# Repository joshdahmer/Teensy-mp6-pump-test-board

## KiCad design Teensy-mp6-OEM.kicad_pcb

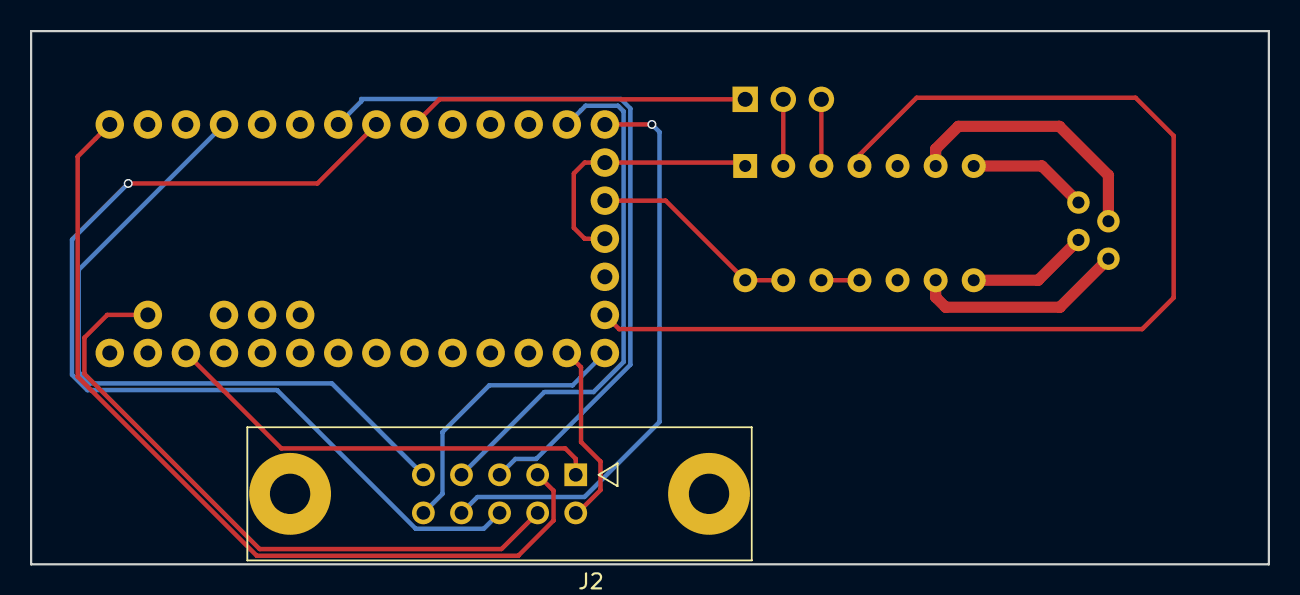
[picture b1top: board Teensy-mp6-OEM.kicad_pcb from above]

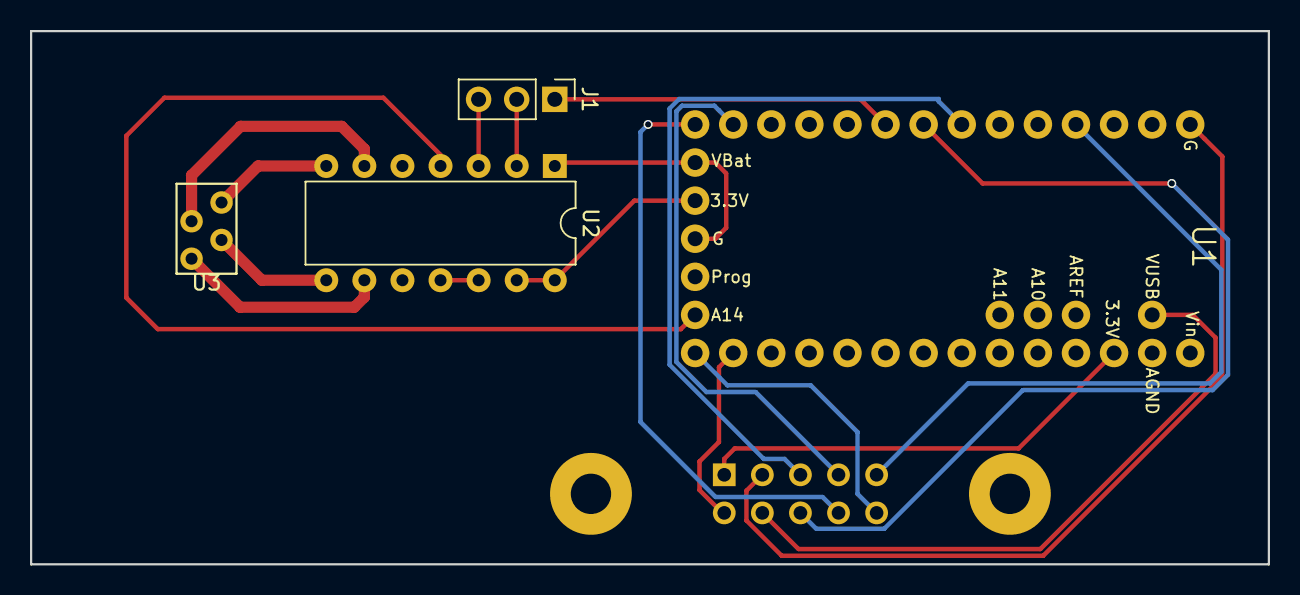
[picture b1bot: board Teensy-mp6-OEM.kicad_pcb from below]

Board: 2 copper layers, 82.6 x 35.6 mm, 5 parts (4 on the bottom side), 20 nets.

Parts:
J1: CONN_01X03; Pin_Header_Straight_1x03_Pitch2.54mm
J2: CONN_02X05; he10-10d
U1: Teensy_3.2; Teensy-3.2
U2: mp6-OEM; DIP-14_W7.62mm
U3: mp6-pump-conector; mp6-pump-footprint

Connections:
+3.3V: J2.1, U1.24
+3V3: U1.31, U2.13, U2.14
+5V(VUSB): J2.4, U1.36
CS_ADC: J2.6, U1.6
CS_POT: J2.5, U1.5
DIN: J2.8, U1.12
DOUT: J2.7, U1.11
FREQ_PIN: J1.1, U1.7
GND: J2.3, U1.27, U1.30, U1.32, U2.1
MONITOR: J2.2, U1.14
unnamed: J1.2, U2.2
unnamed: J1.3, U2.3
unnamed: U1.28, U2.4
unnamed: U2.6, U3.3
unnamed: U2.7, U3.4
unnamed: U2.8, U3.2
unnamed: U2.9, U3.1
unnamed: U2.11, U2.12
SCK: J2.10, U1.13
SHUTTER: J2.9, U1.2

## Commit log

2017-05-25 no message
2017-05-25 updated gitignore
2017-06-15 Increase HV track widths, Change Teensy 3.3V and GND pins, Move Molex Connector
2017-06-23 Added connector from PMT Control Board
2017-07-11 Rewire with different power
